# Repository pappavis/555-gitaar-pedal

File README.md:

# 555-guitaar-pedal
Guitar pedal using NE555 timer chip and LM386 OpAmp

KICAD schema:<br>

door: Michiel Erasmus

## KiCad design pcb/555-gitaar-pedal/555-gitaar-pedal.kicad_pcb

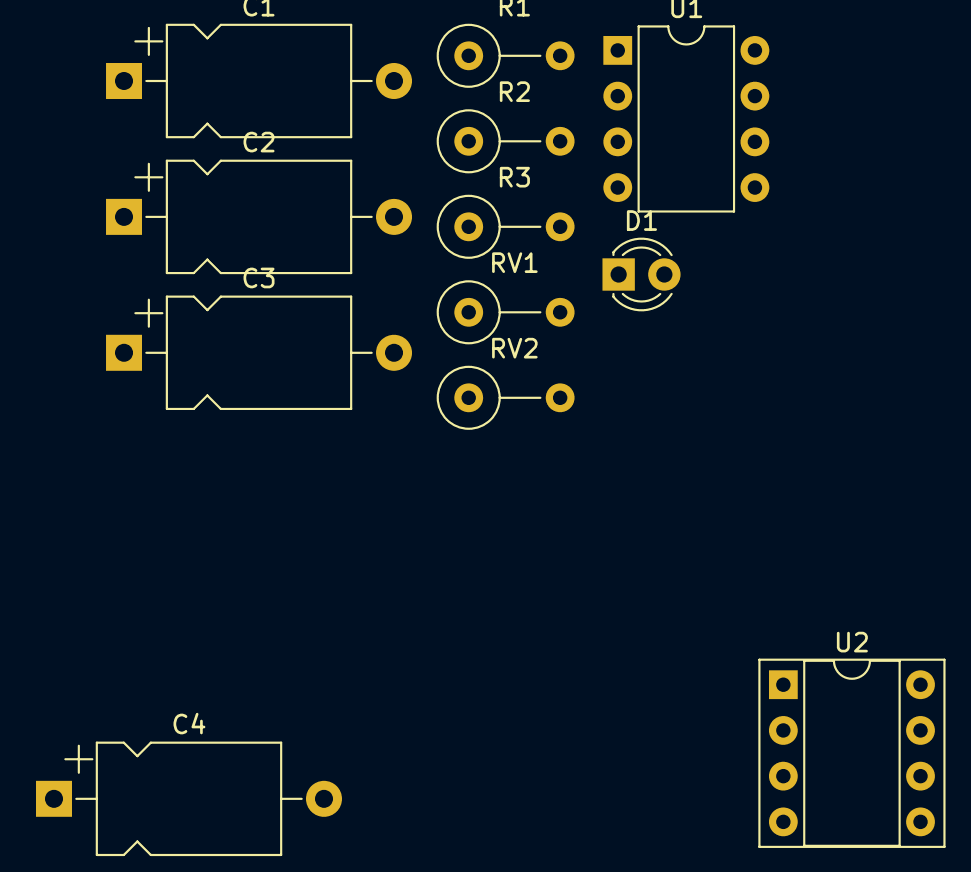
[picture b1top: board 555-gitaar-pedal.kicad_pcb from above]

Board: 2 copper layers, 12 parts (0 on the bottom side), 10 nets, no tracks yet.

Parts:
C1: 10uF; CP_Axial_L10.0mm_D6.0mm_P15.00mm_Horizontal
C2: 1uF; CP_Axial_L10.0mm_D6.0mm_P15.00mm_Horizontal
C3, C4: 220uF; CP_Axial_L10.0mm_D6.0mm_P15.00mm_Horizontal
D1: Tap; LED_D3.0mm
R1, R2, R3: 470; R_Axial_DIN0309_L9.0mm_D3.2mm_P5.08mm_Vertical
RV1, RV2: 100k; R_Axial_DIN0309_L9.0mm_D3.2mm_P5.08mm_Vertical
U1: NE555P; DIP-8_W7.62mm
U2: LM386; DIP-8_W7.62mm_Socket

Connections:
+9V: R2.2, R3.1, R3.2, U1.4 (R), U1.8 (VCC)
GND: C4.2, D1.1 (K), U1.1 (GND), U2.2 (-), U2.4 (GND)
unnamed: C1.1, U2.8 (GAIN)
unnamed: C1.2, U2.1 (GAIN)
unnamed: C2.1, RV1.2
unnamed: C3.1, U2.5
unnamed: D1.2 (A), R1.1, U1.3 (Q)
unnamed: RV2.2, U1.7 (DIS)
unnamed: C2.2, U2.3 (+)
TRIG: C4.1, U1.2 (TR), U1.6 (THR)

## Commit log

2023-09-20 plaatje
2023-09-20 KiCAD schema bijgewerkt
2023-11-20 KiCAD bijgewerkt.
